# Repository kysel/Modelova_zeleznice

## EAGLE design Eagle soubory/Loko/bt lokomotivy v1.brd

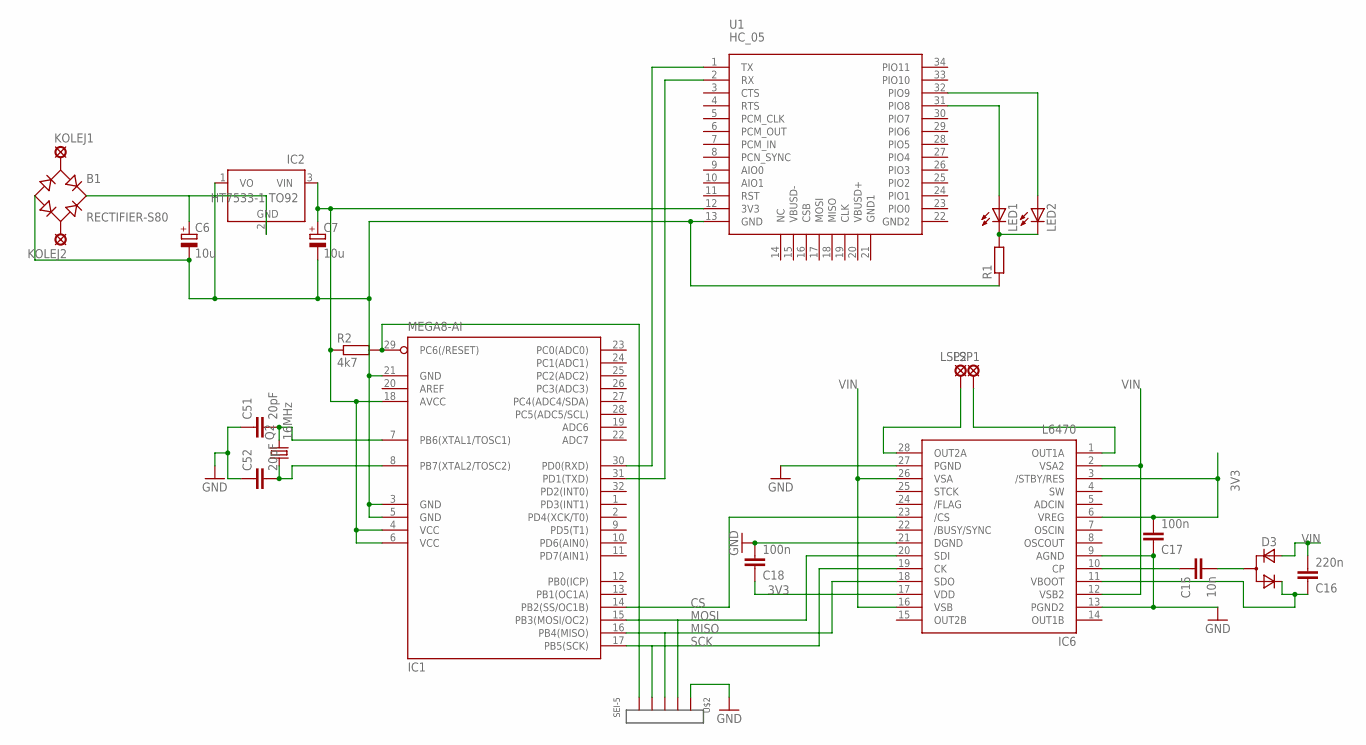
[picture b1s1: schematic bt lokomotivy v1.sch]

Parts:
B1: RECTIFIER-S80; TO-269AA
C6, C7: 10u; 153CLV-0405
C15: 10n; C0603
C16: 220n; C0603K
C17, C18: 100n; C0402
C51, C52: 20pF; C0603
D3: D_ACACSOT323; SOT323
IC1: MEGA8-AI; TQFP32-08
IC2: HT7533-1 TO92; TO92
IC6: L6470; HTSSOP28
KOLEJ1, KOLEJ2: LSP10
LED1, LED2: LEDCHIPLED_0603; CHIPLED_0603
LSP1, LSP2: LSP10
Q2: 16MHz; HC49UP
R1: R-EU_R0603; R0603
R2: 4k7; R0603
U1: HC_05; BLUETOOTH_SMD
U$2: SEI-5

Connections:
3V3: C7.+, C17.2, C18.1, IC1.4 (VCC), IC1.6 (VCC), IC1.18 (AVCC), IC2.3 (VIN), IC6.3 (/STBY/RES), IC6.6 (VREG), IC6.17 (VDD), R2.1, U1.12 (3V3)
CS: IC1.14 (PB2(SS/OC1B)), IC6.23 (/CS)
GND: B1.-, C6.-, C7.-, C17.1, C18.2, C51.1, C52.1, IC1.3 (GND), IC1.5 (GND), IC1.21 (GND), IC2.1 (VO), IC6.9 (AGND), IC6.13 (PGND2), IC6.21 (DGND), IC6.27 (PGND), R1.1, U1.13 (GND), U$2.P$1
MISO: IC1.16 (PB4(MISO)), IC6.18 (SDO), U$2.P$3
MOSI: IC1.15 (PB3(MOSI/OC2)), IC6.20 (SDI), U$2.P$2
unnamed: IC1.30 (PD0(RXD)), U1.1 (TX)
unnamed: LED1.C, LED2.C, R1.2
unnamed: B1.AC1, KOLEJ1.MP
unnamed: B1.AC2, KOLEJ2.MP
unnamed: IC1.31 (PD1(TXD)), U1.2 (RX)
unnamed: IC1.29 (PC6(/RESET)), R2.2, U$2.P$5
unnamed: C51.2, IC1.7 (PB6(XTAL1/TOSC1)), Q2.2
unnamed: C52.2, IC1.8 (PB7(XTAL2/TOSC2)), Q2.1
unnamed: LED1.A, U1.31 (PIO8)
unnamed: LED2.A, U1.32 (PIO9)
unnamed: C15.1, IC6.10 (CP)
unnamed: C15.2, D3.1 (CA)
SCK: IC1.17 (PB5(SCK)), IC6.19 (CK), U$2.P$4
VBOOTX: C16.1, D3.2 (C), IC6.11 (VBOOT)
VIN: B1.+, C6.+, C16.2, D3.3 (A), IC2.2 (GND), IC6.2 (VSA2), IC6.12 (VSB2), IC6.16 (VSB), IC6.26 (VSA)
X1: IC6.1 (OUT1A), LSP1.MP
X2: IC6.28 (OUT2A), LSP2.MP

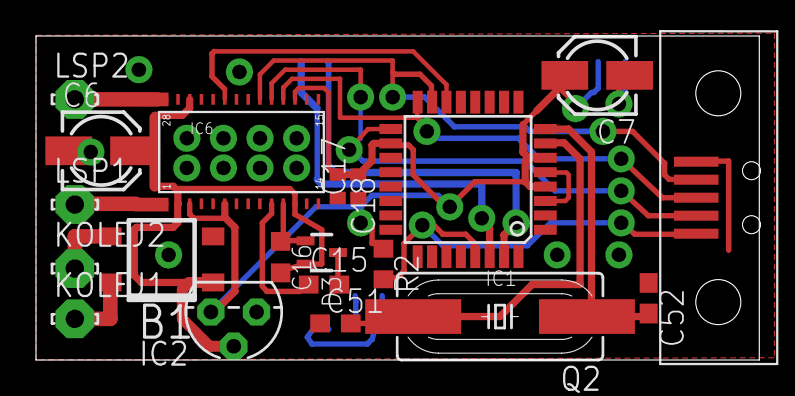
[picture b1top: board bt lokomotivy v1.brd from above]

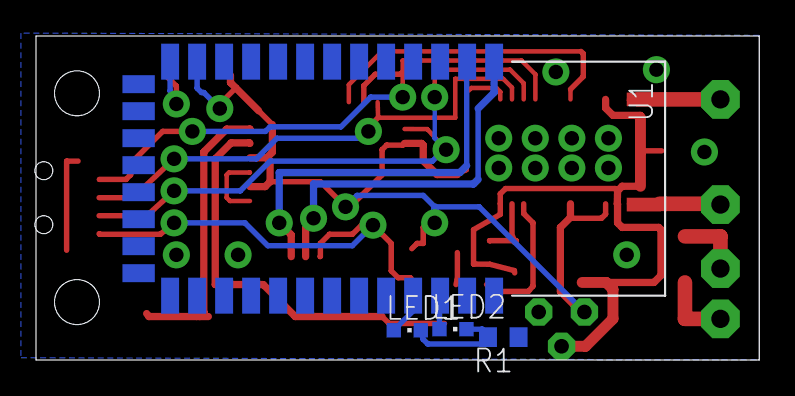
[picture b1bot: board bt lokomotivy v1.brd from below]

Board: 2 copper layers, 40.2 x 18.0 mm, 24 parts (4 on the bottom side), 22 nets.

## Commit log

2013-01-26 Update .gitignore
    aa
2013-01-26 initial
2013-01-26 sync s gd
2013-01-26 del readme
2013-01-26 loko brd + initial avr sources
2013-02-16 added servopřestavník
